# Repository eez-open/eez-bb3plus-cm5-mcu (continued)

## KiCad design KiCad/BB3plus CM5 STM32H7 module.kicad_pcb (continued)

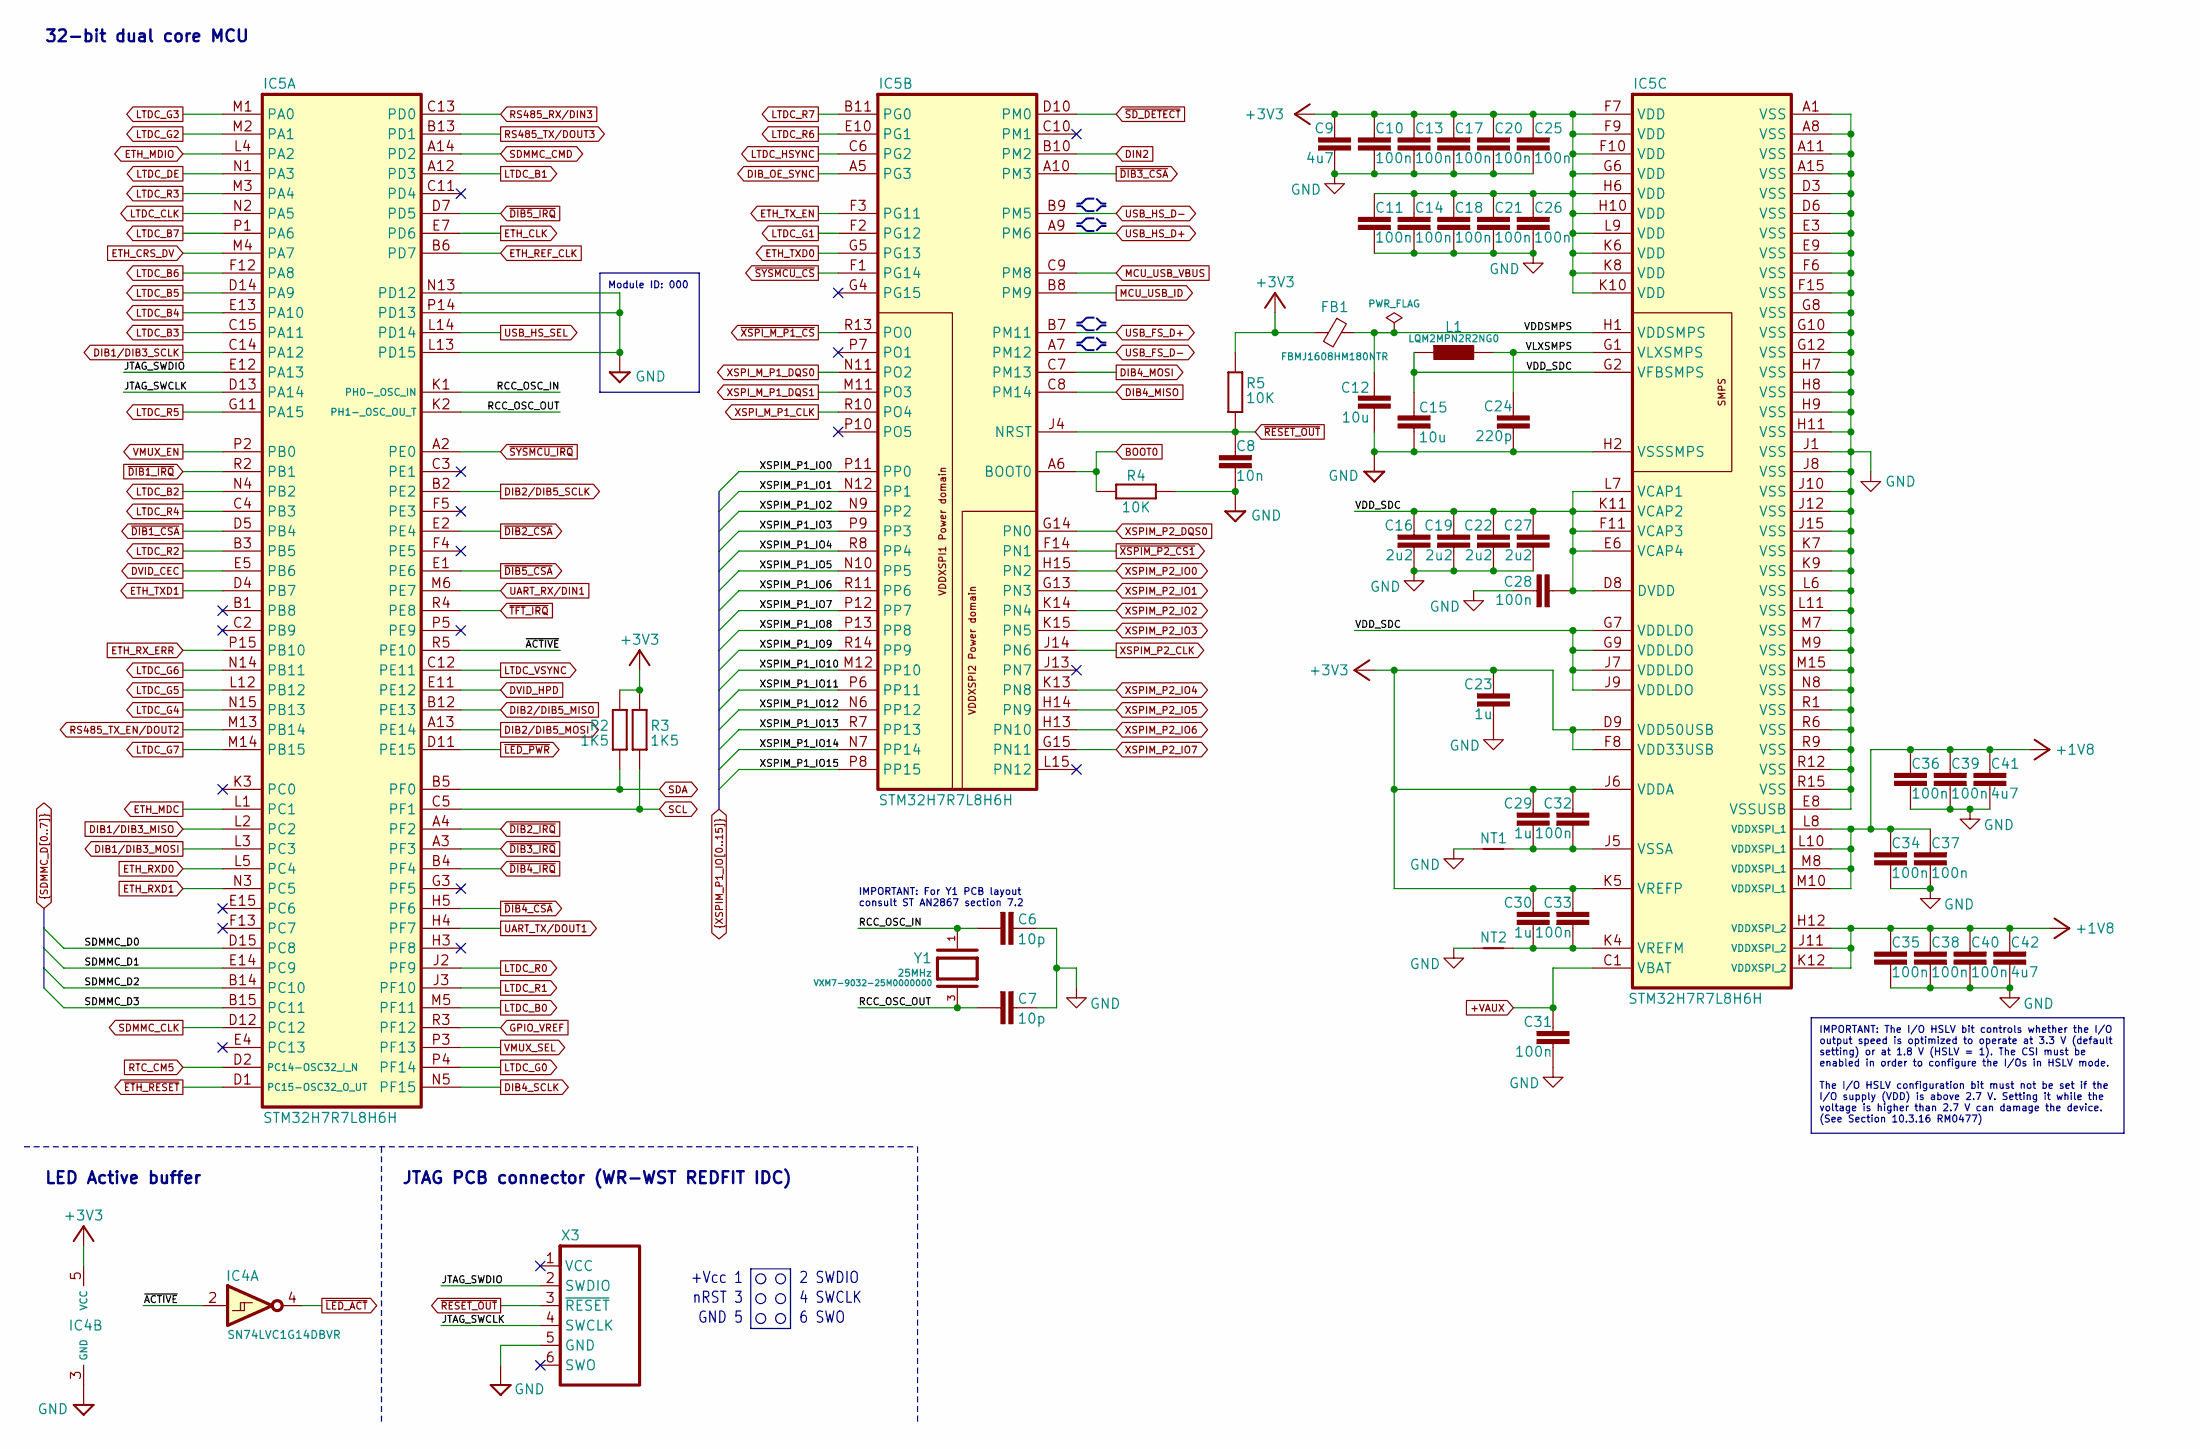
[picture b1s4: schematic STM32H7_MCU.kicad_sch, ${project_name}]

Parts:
C6, C7: 10p; C_0402_1005Metric; DigiKey 490-7299-1-ND
C8: 10n; C_0402_1005Metric; DigiKey 490-6309-1-ND
C9, C41, C42: 4u7; C_0603_1608Metric; DigiKey 1276-1044-1-ND
C10, C11, C13, C14, C17, C18, C20, C21, C25, C26, C28, C31, C32, C33, C34, C35, C36, C37, C38, C39, C40: 100n; C_0402_1005Metric; DigiKey 490-6287-1-ND
C12, C15: 10u; C_0603_1608Metric; DigiKey 1276-1052-6-ND
C16, C19, C22, C27: 2u2; C_0402_1005Metric; DigiKey 490-GRM155C71A225KE11JCT-ND
C23, C29, C30: 1u; C_0402_1005Metric; DigiKey 490-GRM155C81A105MA12DCT-ND
C24: 220p; C_0402_1005Metric; DigiKey 1276-6762-1-ND
FB1: FBMJ1608HM180NTR; BEAD0603; DigiKey 587-3251-2-ND
IC4: SN74LVC1G14DBVR; DBV5; DigiKey 296-11607-1-ND
IC5: STM32H7R7L8H6H; TFBGA225_13X13_STM; DigiKey 497-STM32H7R7L8H6H-ND
L1: LQM2MPN2R2NG0; 0806; DigiKey 490-7786-2-ND
NT1, NT2: NetTie_2; NetTie-2_SMD_Pad0.2mm
R2, R3: 1K5; R_0402_1005Metric; DigiKey 311-1.50KLRCT-ND
R4, R5: 10K; R_0402_1005Metric; DigiKey 311-10.0KLRCT-ND
X3: WR-WST_490107670612_DEBUG_no frame
Y1: VXM7-9032-25M0000000; XTAL_403C11A24M00000; DigiKey 150-VXM7-9032-25M0000000CT-ND

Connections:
+1V8: C34.1, C35.1, C36.1, C37.1, C38.1, C39.1, C40.1, C41.1, C42.1, IC5.H12 (VDDXSPI_2), IC5.J11 (VDDXSPI_2), IC5.K12 (VDDXSPI_2), IC5.L8 (VDDXSPI_1), IC5.L10 (VDDXSPI_1), IC5.M8 (VDDXSPI_1), IC5.M10 (VDDXSPI_1); also elsewhere on the board
+3V3: C9.1, C10.1, C11.1, C13.1, C14.1, C17.1, C18.1, C20.1, C21.1, C23.1, C25.1, C26.1, C29.1, C30.1, C32.1, C33.1, FB1.2, IC4.5 (VCC), IC5.D9 (VDD50USB), IC5.F7 (VDD), IC5.F8 (VDD33USB), IC5.F9 (VDD), IC5.F10 (VDD), IC5.G6 (VDD), IC5.H6 (VDD), IC5.H10 (VDD), IC5.J6 (VDDA), IC5.K5 (VREFP), IC5.K6 (VDD), IC5.K8 (VDD), IC5.K10 (VDD), IC5.L9 (VDD), R2.2, R3.2, R5.2; also elsewhere on the board
+VAUX: C31.1, IC5.C1 (VBAT); also elsewhere on the board
/STM32H7 MCU/JTAG_SWCLK: IC5.D13 (PA14), X3.4 (SWCLK)
/STM32H7 MCU/JTAG_SWDIO: IC5.E12 (PA13), X3.2 (SWDIO)
/STM32H7 MCU/RCC_OSC_IN: C6.2, IC5.K1 (PH0-_OSC_IN), Y1.1
/STM32H7 MCU/RCC_OSC_OUT: C7.2, IC5.K2 (PH1-_OSC_OU_T), Y1.3
/STM32H7 MCU/VDDSMPS: C12.2, FB1.1, IC5.H1 (VDDSMPS)
/STM32H7 MCU/VDD_SDC: C15.2, C16.1, C19.1, C22.1, C27.1, C28.2, IC5.D8 (DVDD), IC5.E6 (VCAP4), IC5.F11 (VCAP3), IC5.G2 (VFBSMPS), IC5.G7 (VDDLDO), IC5.G9 (VDDLDO), IC5.J7 (VDDLDO), IC5.J9 (VDDLDO), IC5.K11 (VCAP2), IC5.L7 (VCAP1), L1.1
/STM32H7 MCU/VLXSMPS: C24.1, IC5.G1 (VLXSMPS), L1.2
/STM32H7 MCU/~ACTIVE: IC4.2 (A), IC5.R5 (PE10)
BOOT0: IC5.A6 (BOOT0), R4.1; also elsewhere on the board
DIB1/DIB3_MISO: IC5.L2 (PC2); also elsewhere on the board
DIB1/DIB3_MOSI: IC5.L3 (PC3); also elsewhere on the board
DIB1/DIB3_SCLK: IC5.C14 (PA12); also elsewhere on the board
DIB2/DIB5_MISO: IC5.B12 (PE13); also elsewhere on the board
DIB2/DIB5_MOSI: IC5.A13 (PE14); also elsewhere on the board
DIB2/DIB5_SCLK: IC5.B2 (PE2); also elsewhere on the board
DIB4_MISO: IC5.C8 (PM14); also elsewhere on the board
DIB4_MOSI: IC5.C7 (PM13); also elsewhere on the board
DIB4_SCLK: IC5.N5 (PF15); also elsewhere on the board
DIB_OE_SYNC: IC5.A5 (PG3); also elsewhere on the board
DIN2: IC5.B10 (PM2); also elsewhere on the board
DVID_CEC: IC5.E5 (PB6); also elsewhere on the board
DVID_HPD: IC5.E11 (PE12); also elsewhere on the board
ETH_CLK: IC5.E7 (PD6); also elsewhere on the board
ETH_CRS_DV: IC5.M4 (PA7); also elsewhere on the board
ETH_MDC: IC5.L1 (PC1); also elsewhere on the board
ETH_MDIO: IC5.L4 (PA2); also elsewhere on the board
ETH_REF_CLK: IC5.B6 (PD7); also elsewhere on the board
ETH_RXD0: IC5.L5 (PC4); also elsewhere on the board
ETH_RXD1: IC5.N3 (PC5); also elsewhere on the board
ETH_RX_ERR: IC5.P15 (PB10); also elsewhere on the board
ETH_TXD0: IC5.G5 (PG13); also elsewhere on the board
ETH_TXD1: IC5.D4 (PB7); also elsewhere on the board
ETH_TX_EN: IC5.F3 (PG11); also elsewhere on the board
GND: C6.1, C7.1, C8.2, C9.2, C10.2, C11.2, C12.1, C13.2, C14.2, C15.1, C16.2, C17.2, C18.2, C19.2, C20.2, C21.2, C22.2, C23.2, C24.2, C25.2, C26.2, C27.2, C28.1, C31.2, C34.2, C35.2, C36.2, C37.2, C38.2, C39.2, C40.2, C41.2, C42.2, IC4.3 (GND), IC5.A1 (VSS), IC5.A8 (VSS), IC5.A11 (VSS), IC5.A15 (VSS), IC5.D3 (VSS), IC5.D6 (VSS), IC5.E3 (VSS), IC5.E8 (VSSUSB), IC5.E9 (VSS), IC5.F6 (VSS), IC5.F15 (VSS), IC5.G8 (VSS), IC5.G10 (VSS), IC5.G12 (VSS), IC5.H2 (VSSSMPS), IC5.H7 (VSS), IC5.H8 (VSS), IC5.H9 (VSS), IC5.H11 (VSS), IC5.J1 (VSS), IC5.J8 (VSS), IC5.J10 (VSS), IC5.J12 (VSS), IC5.J15 (VSS), IC5.K7 (VSS), IC5.K9 (VSS), IC5.L6 (VSS), IC5.L11 (VSS), IC5.L13 (PD15), IC5.M7 (VSS), IC5.M9 (VSS), IC5.M15 (VSS), IC5.N8 (VSS), IC5.N13 (PD12), IC5.P14 (PD13), IC5.R1 (VSS), IC5.R6 (VSS), IC5.R9 (VSS), IC5.R12 (VSS), IC5.R15 (VSS), NT1.1, NT2.1, R4.2, X3.5 (GND); also elsewhere on the board
GPIO_VREF: IC5.R3 (PF12); also elsewhere on the board
LTDC_B0: IC5.M5 (PF11); also elsewhere on the board
LTDC_B1: IC5.A12 (PD3); also elsewhere on the board
LTDC_B2: IC5.N4 (PB2); also elsewhere on the board
LTDC_B3: IC5.C15 (PA11); also elsewhere on the board
LTDC_B4: IC5.E13 (PA10); also elsewhere on the board
LTDC_B5: IC5.D14 (PA9); also elsewhere on the board
LTDC_B6: IC5.F12 (PA8); also elsewhere on the board
LTDC_B7: IC5.P1 (PA6); also elsewhere on the board
LTDC_CLK: IC5.N2 (PA5); also elsewhere on the board
LTDC_DE: IC5.N1 (PA3); also elsewhere on the board
LTDC_G0: IC5.P4 (PF14); also elsewhere on the board
LTDC_G1: IC5.F2 (PG12); also elsewhere on the board
LTDC_G2: IC5.M2 (PA1); also elsewhere on the board
LTDC_G3: IC5.M1 (PA0); also elsewhere on the board
LTDC_G4: IC5.N15 (PB13); also elsewhere on the board
LTDC_G5: IC5.L12 (PB12); also elsewhere on the board
LTDC_G6: IC5.N14 (PB11); also elsewhere on the board
LTDC_G7: IC5.M14 (PB15); also elsewhere on the board
LTDC_HSYNC: IC5.C6 (PG2); also elsewhere on the board
LTDC_R0: IC5.J2 (PF9); also elsewhere on the board
LTDC_R1: IC5.J3 (PF10); also elsewhere on the board
LTDC_R2: IC5.B3 (PB5); also elsewhere on the board
LTDC_R3: IC5.M3 (PA4); also elsewhere on the board
LTDC_R4: IC5.C4 (PB3); also elsewhere on the board
LTDC_R5: IC5.G11 (PA15); also elsewhere on the board
LTDC_R6: IC5.E10 (PG1); also elsewhere on the board
LTDC_R7: IC5.B11 (PG0); also elsewhere on the board
LTDC_VSYNC: IC5.C12 (PE11); also elsewhere on the board
MCU_USB_ID: IC5.B8 (PM9); also elsewhere on the board
MCU_USB_VBUS: IC5.C9 (PM8); also elsewhere on the board
unnamed: C30.2, C33.2, IC5.K4 (VREFM), NT2.2
unnamed: C29.2, C32.2, IC5.J5 (VSSA), NT1.2
RS485_RX/DIN3: IC5.C13 (PD0); also elsewhere on the board
RS485_TX_EN/DOUT2: IC5.M13 (PB14); also elsewhere on the board
RS485_TX/DOUT3: IC5.B13 (PD1); also elsewhere on the board
RTC_CM5: IC5.D2 (PC14-OSC32_I_N); also elsewhere on the board
SCL: IC5.C5 (PF1), R3.1; also elsewhere on the board
SDA: IC5.B5 (PF0), R2.1; also elsewhere on the board
SDMMC_CLK: IC5.D12 (PC12); also elsewhere on the board
SDMMC_CMD: IC5.A14 (PD2); also elsewhere on the board
SDMMC_D0: IC5.D15 (PC8); also elsewhere on the board
SDMMC_D1: IC5.E14 (PC9); also elsewhere on the board
SDMMC_D2: IC5.B14 (PC10); also elsewhere on the board
SDMMC_D3: IC5.B15 (PC11); also elsewhere on the board
UART_RX/DIN1: IC5.M6 (PE7); also elsewhere on the board
UART_TX/DOUT1: IC5.H4 (PF7); also elsewhere on the board
USB_FS_D+: IC5.B7 (PM11); also elsewhere on the board
USB_FS_D-: IC5.A7 (PM12); also elsewhere on the board
USB_HS_D+: IC5.A9 (PM6); also elsewhere on the board
USB_HS_D-: IC5.B9 (PM5); also elsewhere on the board
USB_HS_SEL: IC5.L14 (PD14); also elsewhere on the board
VMUX_EN: IC5.P2 (PB0); also elsewhere on the board
VMUX_SEL: IC5.P3 (PF13); also elsewhere on the board
XSPIM_P1_IO0: IC5.P11 (PP0); also elsewhere on the board
XSPIM_P1_IO1: IC5.N12 (PP1); also elsewhere on the board
XSPIM_P1_IO2: IC5.N9 (PP2); also elsewhere on the board
XSPIM_P1_IO3: IC5.P9 (PP3); also elsewhere on the board
XSPIM_P1_IO4: IC5.R8 (PP4); also elsewhere on the board
XSPIM_P1_IO5: IC5.N10 (PP5); also elsewhere on the board
XSPIM_P1_IO6: IC5.R11 (PP6); also elsewhere on the board
XSPIM_P1_IO7: IC5.P12 (PP7); also elsewhere on the board
XSPIM_P1_IO8: IC5.P13 (PP8); also elsewhere on the board
XSPIM_P1_IO9: IC5.R14 (PP9); also elsewhere on the board
XSPIM_P1_IO10: IC5.M12 (PP10); also elsewhere on the board
XSPIM_P1_IO11: IC5.P6 (PP11); also elsewhere on the board
XSPIM_P1_IO12: IC5.N6 (PP12); also elsewhere on the board
XSPIM_P1_IO13: IC5.R7 (PP13); also elsewhere on the board
XSPIM_P1_IO14: IC5.N7 (PP14); also elsewhere on the board
XSPIM_P1_IO15: IC5.P8 (PP15); also elsewhere on the board
XSPIM_P2_CLK: IC5.J14 (PN6); also elsewhere on the board
XSPIM_P2_DQS0: IC5.G14 (PN0); also elsewhere on the board
XSPIM_P2_IO0: IC5.H15 (PN2); also elsewhere on the board
XSPIM_P2_IO1: IC5.G13 (PN3); also elsewhere on the board
XSPIM_P2_IO2: IC5.K14 (PN4); also elsewhere on the board
XSPIM_P2_IO3: IC5.K15 (PN5); also elsewhere on the board
XSPIM_P2_IO4: IC5.K13 (PN8); also elsewhere on the board
XSPIM_P2_IO5: IC5.H14 (PN9); also elsewhere on the board
XSPIM_P2_IO6: IC5.H13 (PN10); also elsewhere on the board
XSPIM_P2_IO7: IC5.G15 (PN11); also elsewhere on the board
XSPI_M_P1_CLK: IC5.R10 (PO4); also elsewhere on the board
XSPI_M_P1_DQS0: IC5.N11 (PO2); also elsewhere on the board
XSPI_M_P1_DQS1: IC5.M11 (PO3); also elsewhere on the board
~DIB1_CSA: IC5.D5 (PB4); also elsewhere on the board
~DIB1_IRQ: IC5.R2 (PB1); also elsewhere on the board
~DIB2_CSA: IC5.E2 (PE4); also elsewhere on the board
~DIB2_IRQ: IC5.A4 (PF2); also elsewhere on the board
~DIB3_CSA: IC5.A10 (PM3); also elsewhere on the board
~DIB3_IRQ: IC5.A3 (PF3); also elsewhere on the board
~DIB4_CSA: IC5.H5 (PF6); also elsewhere on the board
~DIB4_IRQ: IC5.B4 (PF4); also elsewhere on the board
~DIB5_CSA: IC5.E1 (PE6); also elsewhere on the board
~DIB5_IRQ: IC5.D7 (PD5); also elsewhere on the board
~ETH_RESET: IC5.D1 (PC15-OSC32_O_UT); also elsewhere on the board
~LED_ACT: IC4.4 (Y); also elsewhere on the board
~LED_PWR: IC5.D11 (PE15); also elsewhere on the board
~RESET_OUT: C8.1, IC5.J4 (NRST), R5.1, X3.3 (~RESET); also elsewhere on the board
~SD_DETECT: IC5.D10 (PM0); also elsewhere on the board
~SYSMCU_CS: IC5.F1 (PG14); also elsewhere on the board
~SYSMCU_IRQ: IC5.A2 (PE0); also elsewhere on the board
~TFT_IRQ: IC5.R4 (PE8); also elsewhere on the board
~XSPIM_P2_CS1: IC5.F14 (PN1); also elsewhere on the board
~XSPI_M_P1_CS: IC5.R13 (PO0); also elsewhere on the board

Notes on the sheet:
2 SWDIO
32-bit dual core MCU
LED Active buffer
4 SWCLK
6 SWO
JTAG PCB connector (WR-WST REDFIT IDC)
nRST 3
IMPORTANT: For Y1 PCB layout consult ST AN2867 section 7.2
+Vcc 1
GND 5
IMPORTANT: The I/O HSLV bit controls whether the I/O output speed is optimized to operate at 3.3 V (default setting) or at 1.8 V (HSLV = 1). The CSI must be enabled in order to configure the I/Os in HSLV mode. The I/O HSLV configuration bit must not be set if the I/O supply (VDD) is above 2.7 V. Se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
Module ID: 000

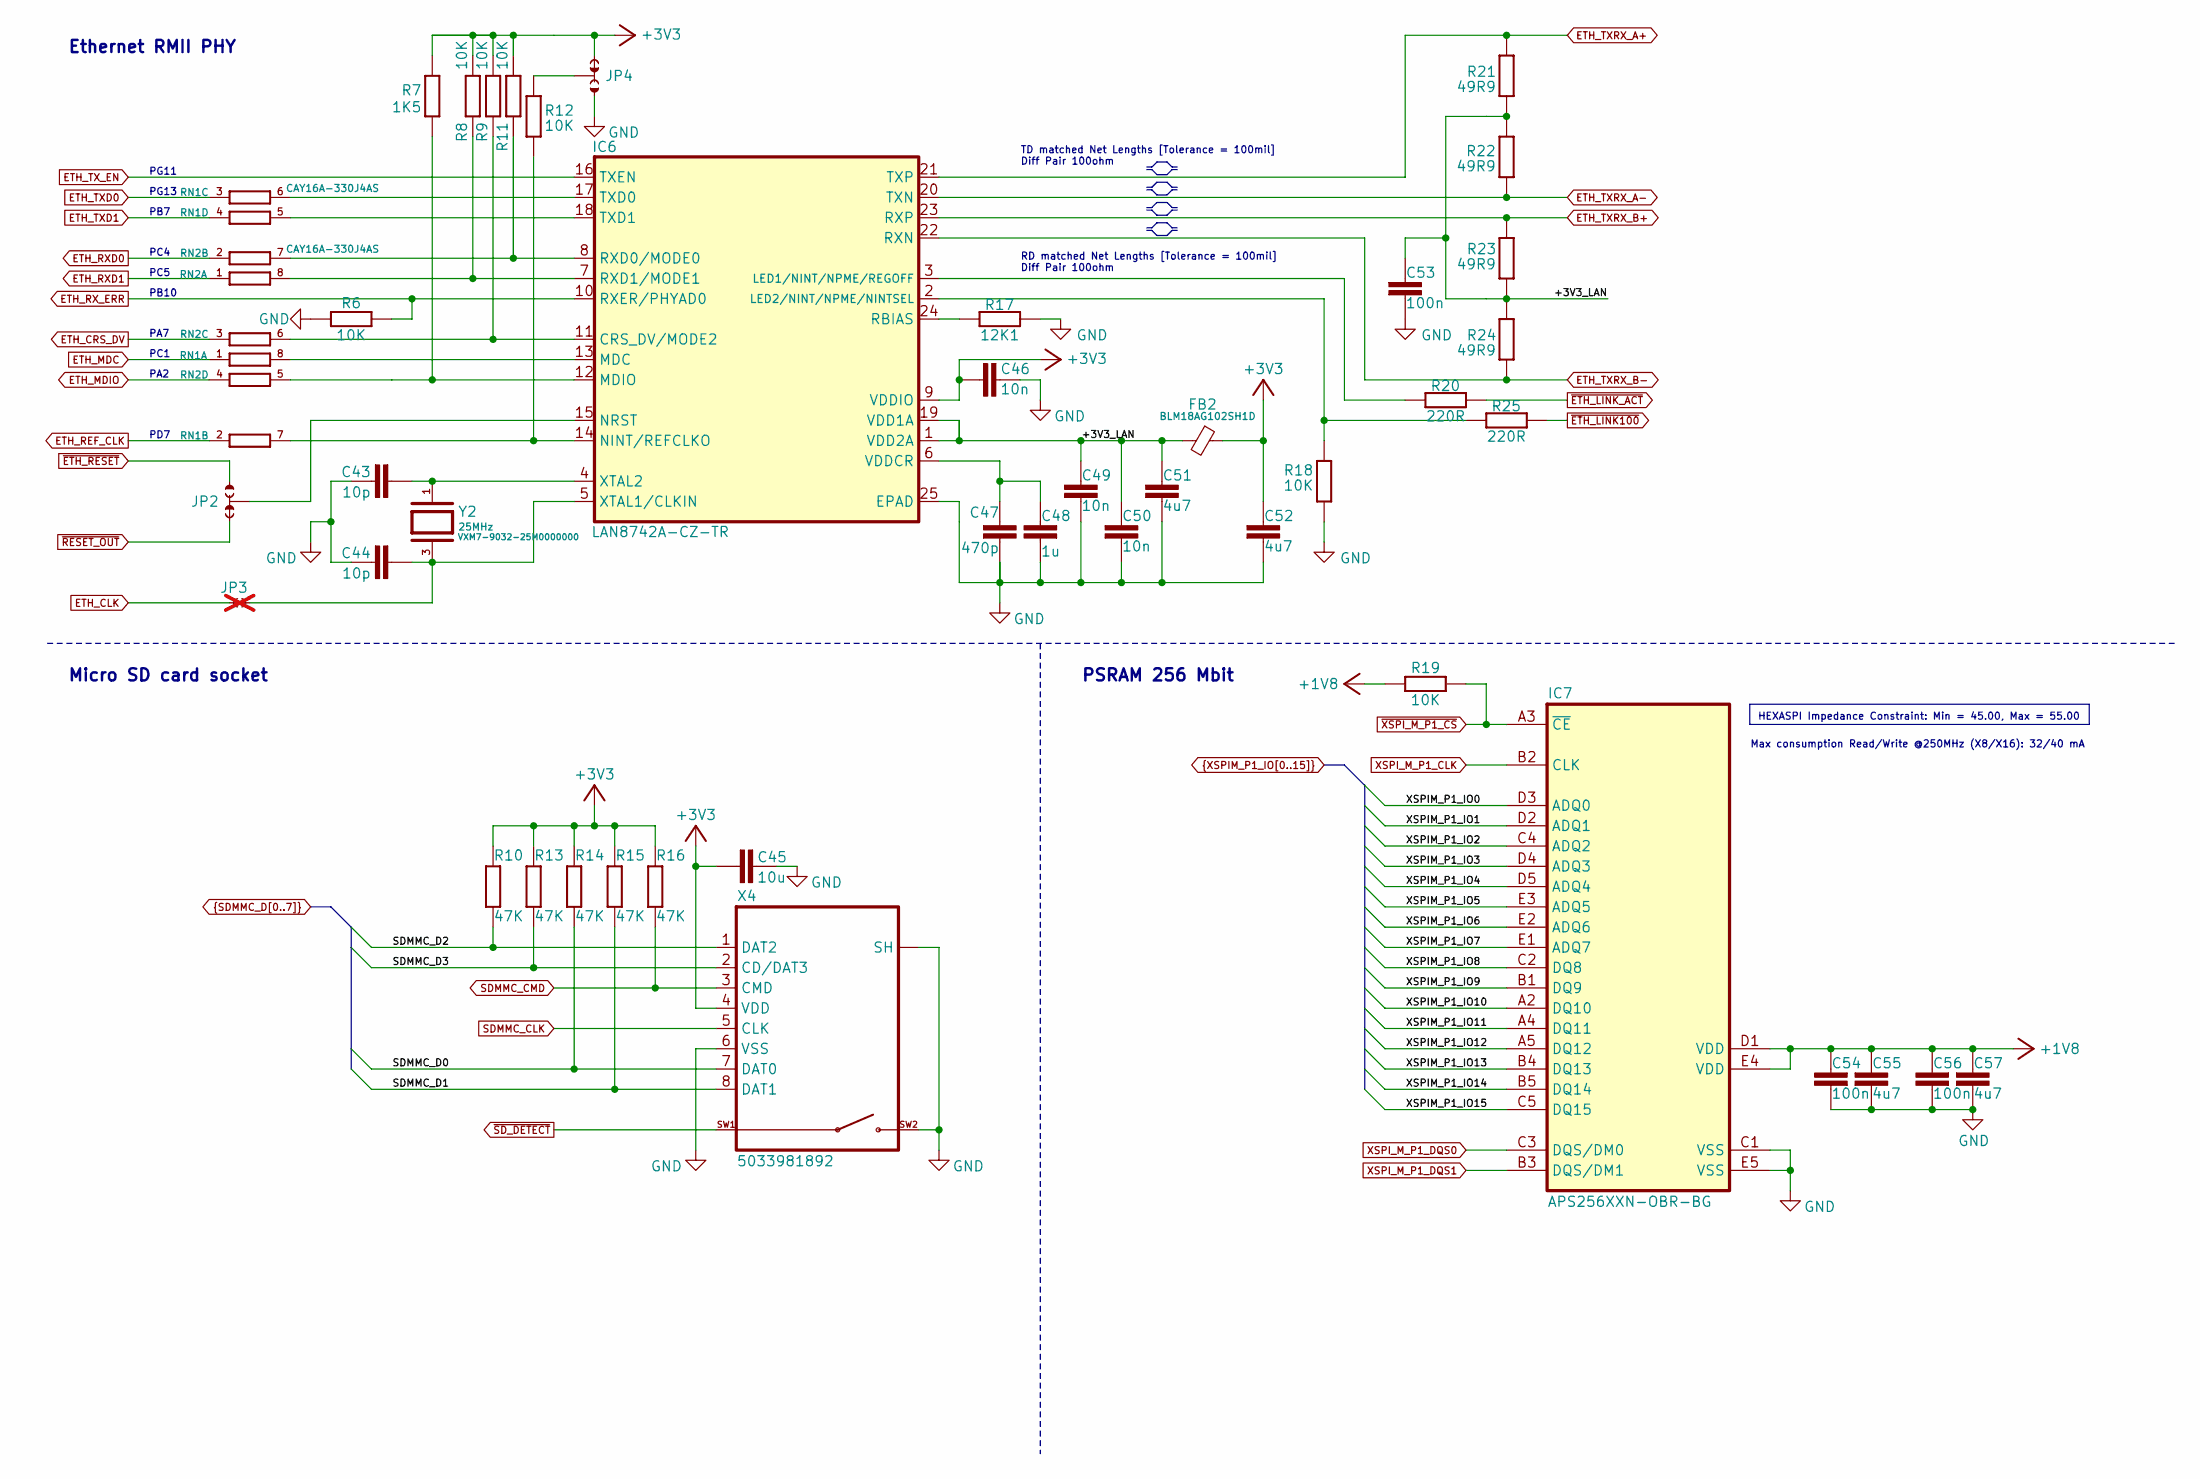
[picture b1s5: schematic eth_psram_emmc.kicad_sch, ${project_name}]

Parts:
C43, C44: 10p; C_0402_1005Metric; DigiKey 490-7299-1-ND
C45: 10u; C_0603_1608Metric; DigiKey 1276-1052-6-ND
C46, C49, C50: 10n; C_0402_1005Metric; DigiKey 490-6309-1-ND
C47: 470p; C_0402_1005Metric; DigiKey 1276-1117-1-ND
C48: 1u; C_0402_1005Metric; DigiKey 490-GRM155C81A105MA12DCT-ND
C51, C52, C55, C57: 4u7; C_0603_1608Metric; DigiKey 1276-1044-1-ND
C53, C54, C56: 100n; C_0402_1005Metric; DigiKey 490-6287-1-ND
FB2: BLM18AG102SH1D; BEAD0603; DigiKey 490-7809-1-ND
IC6: LAN8742A-CZ-TR; SQFN24_4X4MC_MCH-M; DigiKey LAN8742A-CZ-CT-ND
IC7: APS256XXN-OBR-BG; APS256XXN-OBR-BG_APY-L; Mouser 878-APS256XXN-OB9-BG
JP2, JP4: JP3 shorted (0603)
JP3: JP2 open (0402); not fitted
R6, R8, R9, R11, R12, R18, R19: 10K; R_0402_1005Metric; DigiKey 311-10.0KLRCT-ND
R7: 1K5; R_0402_1005Metric; DigiKey 311-1.50KLRCT-ND
R10, R13, R14, R15, R16: 47K; R_0402_1005Metric; DigiKey 311-47.0KLRCT-ND
R17: 12K1; R_0402_1005Metric; DigiKey 13-RC0402FR-1012K1LCT-ND
R20, R25: 220R; R_0402_1005Metric; DigiKey 311-220LRCT-ND
R21, R22, R23, R24: 49R9; R_0402_1005Metric; DigiKey 13-RC0402FR-1349R9LCT-ND
RN1, RN2: CAY16A-330J4AS; CAY16; DigiKey CAY16-330J4LFCT-ND
X4: 5033981892; DigiKey WM11190CT-ND
Y2: VXM7-9032-25M0000000; XTAL_403C11A24M00000; DigiKey 150-VXM7-9032-25M0000000CT-ND

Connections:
+1V8: C54.1, C55.1, C56.1, C57.1, IC7.D1 (VDD), IC7.E4 (VDD), R19.2; also elsewhere on the board
+3V3: C45.2, C46.1, C52.1, FB2.1, IC6.9 (VDDIO), JP4.NC, R7.2, R8.1, R9.2, R10.1, R11.2, R13.1, R14.1, R15.1, R16.1, X4.4 (VDD); also elsewhere on the board
/Ethernet PHY, PSRAM, SDcard/+3V3_LAN: C49.1, C50.1, C51.1, C53.2, FB2.2, IC6.1 (VDD2A), IC6.19 (VDD1A), R21.1, R22.1, R23.1, R24.2
ETH_CLK: JP3.1; also elsewhere on the board
ETH_CRS_DV: RN2.3 (1); also elsewhere on the board
ETH_MDC: RN1.1; also elsewhere on the board
ETH_MDIO: RN2.4 (1); also elsewhere on the board
ETH_REF_CLK: RN1.2 (1); also elsewhere on the board
ETH_RXD0: RN2.2 (1); also elsewhere on the board
ETH_RXD1: RN2.1; also elsewhere on the board
ETH_RX_ERR: IC6.10 (RXER/PHYAD0), R6.1; also elsewhere on the board
ETH_TXD0: RN1.3 (1); also elsewhere on the board
ETH_TXD1: RN1.4 (1); also elsewhere on the board
ETH_TXRX_A+: IC6.21 (TXP), R21.2; also elsewhere on the board
ETH_TXRX_A-: IC6.20 (TXN), R22.2; also elsewhere on the board
ETH_TXRX_B+: IC6.23 (RXP), R23.2; also elsewhere on the board
ETH_TXRX_B-: IC6.22 (RXN), R24.1; also elsewhere on the board
ETH_TX_EN: IC6.16 (TXEN); also elsewhere on the board
GND: C43.1, C44.1, C45.1, C46.2, C47.2, C48.1, C49.2, C50.2, C51.2, C52.2, C53.1, C54.2, C55.2, C56.2, C57.2, IC6.25 (EPAD), IC7.C1 (VSS), IC7.E5 (VSS), JP4.NO, R6.2, R17.2, R18.2, X4.6 (VSS), X4.SH, X4.SW2; also elsewhere on the board
unnamed: IC6.11 (CRS_DV/MODE2), R9.1, RN2.6 (2)
unnamed: IC6.3 (LED1/NINT/NPME/REGOFF), R20.1
unnamed: IC6.2 (LED2/NINT/NPME/NINTSEL), R18.1, R25.1
unnamed: IC6.13 (MDC), RN1.8 (2)
unnamed: IC6.12 (MDIO), R7.1, RN2.5 (2)
unnamed: IC6.14 (NINT/REFCLKO), R12.1, RN1.7 (2)
unnamed: IC6.15 (NRST), JP2.COM
unnamed: IC6.24 (RBIAS), R17.1
unnamed: IC6.8 (RXD0/MODE0), R11.1, RN2.7 (2)
unnamed: IC6.7 (RXD1/MODE1), R8.2, RN2.8 (2)
unnamed: IC6.17 (TXD0), RN1.6 (2)
unnamed: IC6.18 (TXD1), RN1.5 (2)
unnamed: C47.1, C48.2, IC6.6 (VDDCR)
unnamed: C44.2, IC6.5 (XTAL1/CLKIN), JP3.2, Y2.3
unnamed: C43.2, IC6.4 (XTAL2), Y2.1
unnamed: JP4.COM, R12.2
SDMMC_CLK: X4.5 (CLK); also elsewhere on the board
SDMMC_CMD: R16.2, X4.3 (CMD); also elsewhere on the board
SDMMC_D0: R14.2, X4.7 (DAT0); also elsewhere on the board
SDMMC_D1: R15.2, X4.8 (DAT1); also elsewhere on the board
SDMMC_D2: R10.2, X4.1 (DAT2); also elsewhere on the board
SDMMC_D3: R13.2, X4.2 (CD/DAT3); also elsewhere on the board
XSPIM_P1_IO0: IC7.D3 (ADQ0); also elsewhere on the board
XSPIM_P1_IO1: IC7.D2 (ADQ1); also elsewhere on the board
XSPIM_P1_IO2: IC7.C4 (ADQ2); also elsewhere on the board
XSPIM_P1_IO3: IC7.D4 (ADQ3); also elsewhere on the board
XSPIM_P1_IO4: IC7.D5 (ADQ4); also elsewhere on the board
XSPIM_P1_IO5: IC7.E3 (ADQ5); also elsewhere on the board
XSPIM_P1_IO6: IC7.E2 (ADQ6); also elsewhere on the board
XSPIM_P1_IO7: IC7.E1 (ADQ7); also elsewhere on the board
XSPIM_P1_IO8: IC7.C2 (DQ8); also elsewhere on the board
XSPIM_P1_IO9: IC7.B1 (DQ9); also elsewhere on the board
XSPIM_P1_IO10: IC7.A2 (DQ10); also elsewhere on the board
XSPIM_P1_IO11: IC7.A4 (DQ11); also elsewhere on the board
XSPIM_P1_IO12: IC7.A5 (DQ12); also elsewhere on the board
XSPIM_P1_IO13: IC7.B4 (DQ13); also elsewhere on the board
XSPIM_P1_IO14: IC7.B5 (DQ14); also elsewhere on the board
XSPIM_P1_IO15: IC7.C5 (DQ15); also elsewhere on the board
XSPI_M_P1_CLK: IC7.B2 (CLK); also elsewhere on the board
XSPI_M_P1_DQS0: IC7.C3 (DQS/DM0); also elsewhere on the board
XSPI_M_P1_DQS1: IC7.B3 (DQS/DM1); also elsewhere on the board
~ETH_LINK100: R25.2; also elsewhere on the board
~ETH_LINK_ACT: R20.2; also elsewhere on the board
~ETH_RESET: JP2.NO; also elsewhere on the board
~RESET_OUT: JP2.NC; also elsewhere on the board
~SD_DETECT: X4.SW1; also elsewhere on the board
~XSPI_M_P1_CS: IC7.A3 (~CE), R19.1; also elsewhere on the board

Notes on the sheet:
PD7
PG11
TD matched Net Lengths [Tolerance = 100mil] Diff Pair 100ohm
Micro SD card socket
PG13
PA7
PB10
PSRAM 256 Mbit
Max consumption Read/Write @250MHz (X8/X16): 32/40 mA
PC4
PB7
PA2
Ethernet RMII PHY
RD matched Net Lengths [Tolerance = 100mil] Diff Pair 100ohm
PC5
PC1
HEXASPI Impedance Constraint: Min = 45.00, Max = 55.00

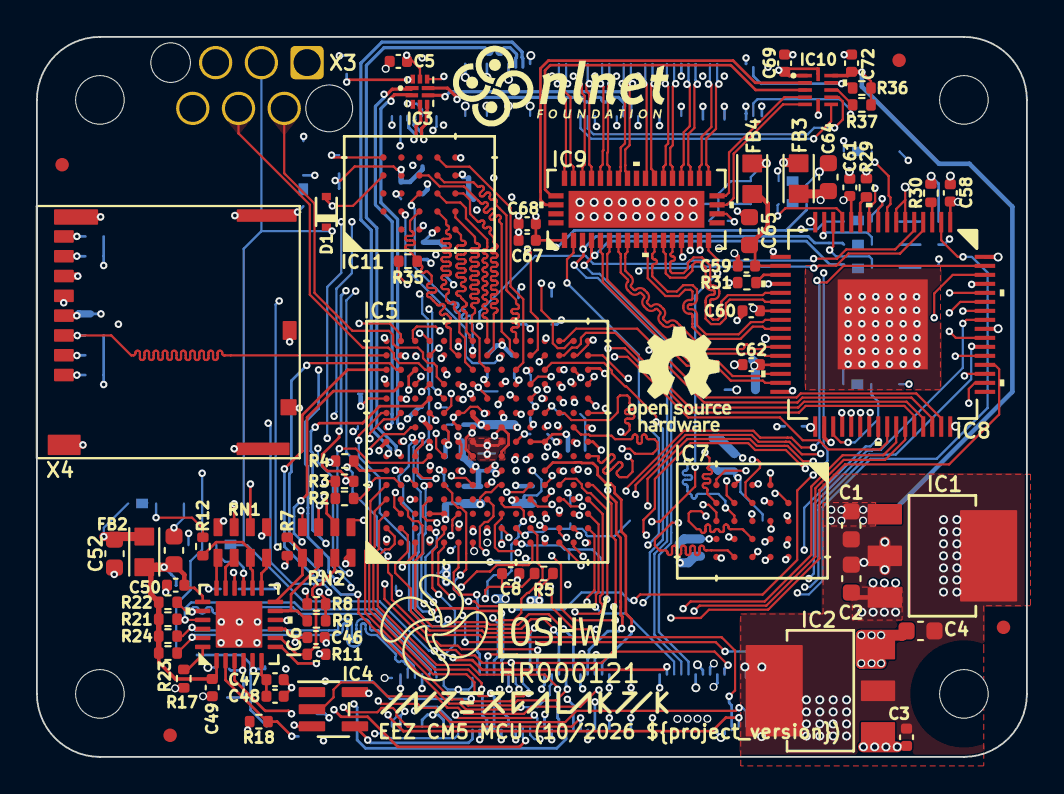
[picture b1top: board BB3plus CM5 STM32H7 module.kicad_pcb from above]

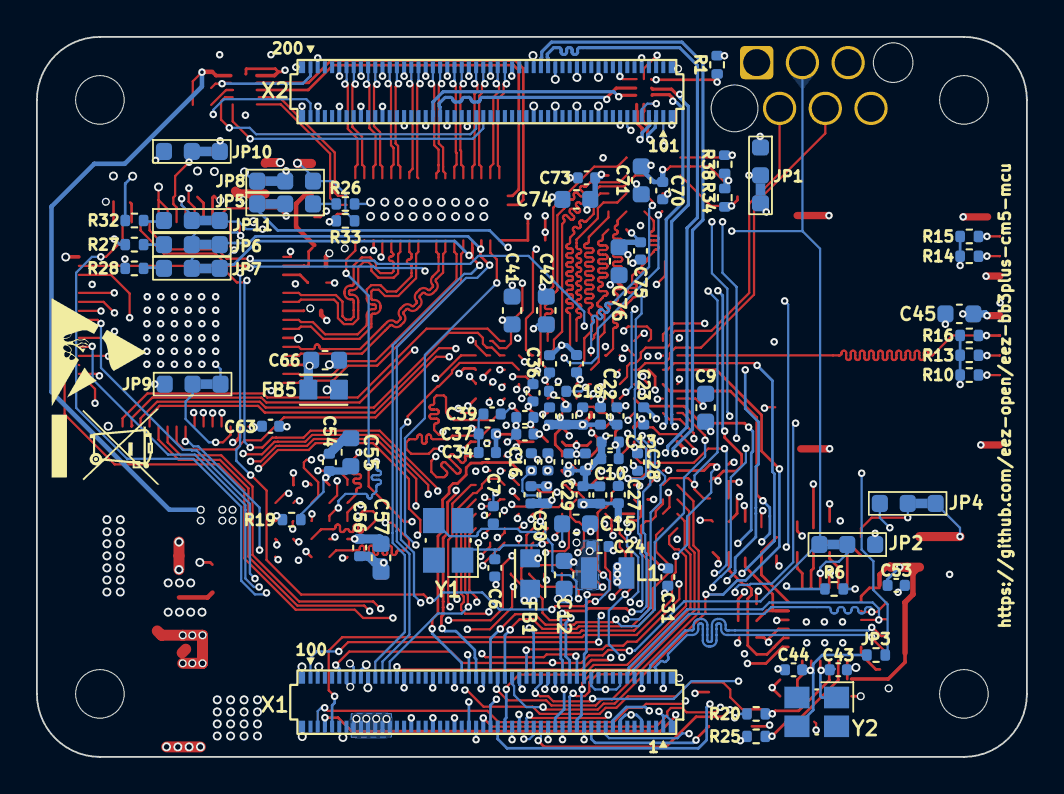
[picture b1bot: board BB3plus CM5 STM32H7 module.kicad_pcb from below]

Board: 6 copper layers, 55.0 x 40.0 mm, 164 parts (89 on the bottom side), 221 nets.

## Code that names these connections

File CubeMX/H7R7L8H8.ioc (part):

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Mcu.Name=STM32H7R7L8HxH
Mcu.Package=TFBGA225 HEXA SMPS
Mcu.UserName=STM32H7R7L8HxH
PA0.GPIOParameters=PinAttribute
PA0.Mode=RGB888
PA0.PinAttribute=Appli
PA0.Signal=LTDC_G3
PA1.GPIOParameters=PinAttribute
PA1.Mode=RGB888
PA1.PinAttribute=Appli
PA1.Signal=LTDC_G2
PA10.GPIOParameters=PinAttribute
PA10.Mode=RGB888
PA10.PinAttribute=Appli
PA10.Signal=LTDC_B4
PA11.GPIOParameters=PinAttribute
PA11.Mode=RGB888
PA11.PinAttribute=Appli
PA11.Signal=LTDC_B3
PA12.GPIOParameters=GPIO_Label,PinAttribute
PA12.GPIO_Label=DIB1/DIB3_SCK
PA12.Mode=Full_Duplex_Master
PA12.PinAttribute=Appli
PA12.Signal=SPI2_SCK
PA13(JTMS/SWDIO).GPIOParameters=GPIO_Label
PA13(JTMS/SWDIO).GPIO_Label=SWDIO
PA13(JTMS/SWDIO).Mode=Serial_Wire
PA13(JTMS/SWDIO).Signal=DEBUG_JTMS-SWDIO
PA14(JTCK/SWCLK).GPIOParameters=GPIO_Label
PA14(JTCK/SWCLK).GPIO_Label=SWCLK
PA14(JTCK/SWCLK).Mode=Serial_Wire
PA14(JTCK/SWCLK).Signal=DEBUG_JTCK-SWCLK
PA15(JTDI).GPIOParameters=PinAttribute
PA15(JTDI).Mode=RGB888
PA15(JTDI).PinAttribute=Appli
PA15(JTDI).Signal=LTDC_R5
PA2.GPIOParameters=GPIO_Speed,PinAttribute
PA2.GPIO_Speed=GPIO_SPEED_FREQ_LOW
PA2.Mode=RMII
PA2.PinAttribute=Appli
PA2.Signal=ETH_MDIO
PA3.GPIOParameters=PinAttribute
PA3.Mode=RGB888
PA3.PinAttribute=Appli
PA3.Signal=LTDC_DE
PA4.GPIOParameters=PinAttribute
PA4.Mode=RGB888
PA4.PinAttribute=Appli
PA4.Signal=LTDC_R3
PA5.GPIOParameters=PinAttribute
PA5.Mode=RGB888
PA5.PinAttribute=Appli
PA5.Signal=LTDC_CLK
PA6.GPIOParameters=PinAttribute
PA6.Mode=RGB888
PA6.PinAttribute=Appli
PA6.Signal=LTDC_B7
PA7.GPIOParameters=GPIO_Speed,PinAttribute
PA7.GPIO_Speed=GPIO_SPEED_FREQ_LOW
PA7.Mode=RMII
PA7.PinAttribute=Appli
PA7.Signal=ETH_RMII_CRS_DV
PA8.GPIOParameters=PinAttribute
PA8.Mode=RGB888
PA8.PinAttribute=Appli
PA8.Signal=LTDC_B6
PA9.GPIOParameters=PinAttribute
PA9.Mode=RGB888
PA9.PinAttribute=Appli
PA9.Signal=LTDC_B5
PB0.ContextOwner=Appli
PB0.GPIOParameters=GPIO_Label,PinAttribute
PB0.GPIO_Label=VMUX_EN
PB0.PinAttribute=Appli
PB0.Signal=GPIO_Output
PB1.ContextOwner=Appli
PB1.GPIOParameters=GPIO_Label,PinAttribute
PB1.GPIO_Label=DIB1_IRQ
PB1.PinAttribute=Appli
PB1.Signal=GPXTI1
PB10.GPIOParameters=PinAttribute
PB10.PinAttribute=Appli
PB10.Signal=ETH_MII_RX_ER
PB11.GPIOParameters=PinAttribute
PB11.Mode=RGB888
PB11.PinAttribute=Appli
PB11.Signal=LTDC_G6
PB12.GPIOParameters=PinAttribute
PB12.Mode=RGB888
PB12.PinAttribute=Appli
PB12.Signal=LTDC_G5
PB13.GPIOParameters=PinAttribute
PB13.Mode=RGB888
PB13.PinAttribute=Appli
PB13.Signal=LTDC_G4
PB14.GPIOParameters=GPIO_Label,PinAttribute
PB14.GPIO_Label=RS485_TX_EN/DOUT2
PB14.Mode=Hardware Flow Control (RS485)
PB14.PinAttribute=Appli
PB14.Signal=UART4_DE
PB15.GPIOParameters=PinAttribute
PB15.Mode=RGB888
PB15.PinAttribute=Appli
PB15.Signal=LTDC_G7
PB2.GPIOParameters=PinAttribute
PB2.Mode=RGB888
PB2.PinAttribute=Appli
PB2.Signal=LTDC_B2
PB3(JTDO/TRACESWO).GPIOParameters=PinAttribute
PB3(JTDO/TRACESWO).Mode=RGB888
PB3(JTDO/TRACESWO).PinAttribute=Appli
PB3(JTDO/TRACESWO).Signal=LTDC_R4
PB4(NJTRST).GPIOParameters=GPIO_Label,PinAttribute
PB4(NJTRST).GPIO_Label=DIB1_CSA
PB4(NJTRST).Mode=NSS_Signal_Hard_Output
PB4(NJTRST).PinAttribute=Appli
PB4(NJTRST).Signal=SPI2_NSS
PB5.GPIOParameters=PinAttribute
PB5.Mode=RGB888
PB5.PinAttribute=Appli
PB5.Signal=LTDC_R2
PB6.GPIOParameters=GPIO_Label,PinAttribute
PB6.GPIO_Label=DVID_CEC
PB6.Mode=CEC_Activate
PB6.PinAttribute=Appli
PB6.Signal=CEC
PB7.GPIOParameters=GPIO_Speed,PinAttribute
PB7.GPIO_Speed=GPIO_SPEED_FREQ_LOW
PB7.Mode=RMII
PB7.PinAttribute=Appli
PB7.Signal=ETH_RMII_TXD1
PB8.GPIOParameters=PinAttribute
PB8.PinAttribute=Appli
PB8.Signal=SDMMC1_D4
PB9.GPIOParameters=PinAttribute
PB9.PinAttribute=Appli
PB9.Signal=SDMMC1_D5
PC1.GPIOParameters=GPIO_Speed,PinAttribute
PC1.GPIO_Speed=GPIO_SPEED_FREQ_LOW
PC1.Mode=RMII
PC1.PinAttribute=Appli
PC1.Signal=ETH_MDC
PC10.GPIOParameters=PinAttribute
PC10.Mode=SD_4_bits_Wide_bus
PC10.PinAttribute=Appli
PC10.Signal=SDMMC1_D2
PC11.GPIOParameters=PinAttribute
PC11.Mode=SD_4_bits_Wide_bus
PC11.PinAttribute=Appli
PC11.Signal=SDMMC1_D3
PC12.GPIOParameters=PinAttribute
PC12.Mode=SD_4_bits_Wide_bus
PC12.PinAttribute=Appli
PC12.Signal=SDMMC1_CK
PC14-OSC32_IN(OSC32_IN).Mode=LSE-External-Clock-Source
PC14-OSC32_IN(OSC32_IN).Signal=RCC_OSC32_IN
PC15-OSC32_OUT(OSC32_OUT).GPIOParameters=GPIO_Label
PC15-OSC32_OUT(OSC32_OUT).GPIO_Label=ETH_RESET
PC15-OSC32_OUT(OSC32_OUT).Signal=GPIO_Output
PC2.GPIOParameters=GPIO_Label,PinAttribute
PC2.GPIO_Label=DIB1/DIB3_MISO
PC2.Mode=Full_Duplex_Master
PC2.PinAttribute=Appli
PC2.Signal=SPI2_MISO
PC3.GPIOParameters=GPIO_Label,PinAttribute
PC3.GPIO_Label=DIB1/DIB3_MOSI
PC3.Mode=Full_Duplex_Master
PC3.PinAttribute=Appli
PC3.Signal=SPI2_MOSI
PC4.GPIOParameters=GPIO_Speed,PinAttribute
PC4.GPIO_Speed=GPIO_SPEED_FREQ_LOW
PC4.Mode=RMII
PC4.PinAttribute=Appli
PC4.Signal=ETH_RMII_RXD0
PC5.GPIOParameters=GPIO_Speed,PinAttribute
PC5.GPIO_Speed=GPIO_SPEED_FREQ_LOW
PC5.Mode=RMII
PC5.PinAttribute=Appli
PC5.Signal=ETH_RMII_RXD1
PC6.GPIOParameters=PinAttribute
PC6.PinAttribute=Appli
PC6.Signal=SDMMC1_D6
PC7.GPIOParameters=PinAttribute
PC7.PinAttribute=Appli
PC7.Signal=SDMMC1_D7
PC8.GPIOParameters=PinAttribute
PC8.Mode=SD_4_bits_Wide_bus
PC8.PinAttribute=Appli
PC8.Signal=SDMMC1_D0
PC9.GPIOParameters=PinAttribute
PC9.Mode=SD_4_bits_Wide_bus
PC9.PinAttribute=Appli
PC9.Signal=SDMMC1_D1
PD0.GPIOParameters=GPIO_Label,PinAttribute
PD0.GPIO_Label=RS485_RX/DIN3
PD0.Mode=Asynchronous
PD0.PinAttribute=Appli
PD0.Signal=UART4_RX
PD1.GPIOParameters=GPIO_Label,PinAttribute
PD1.GPIO_Label=RS485_TX/DOUT3
PD1.Mode=Asynchronous
PD1.PinAttribute=Appli
PD1.Signal=UART4_TX
PD14.ContextOwner=Appli
PD14.GPIOParameters=GPIO_Label,PinAttribute
PD14.GPIO_Label=USB_FS_SEL
PD14.PinAttribute=Appli
PD14.Signal=GPIO_Output
PD2.GPIOParameters=PinAttribute
PD2.Mode=SD_4_bits_Wide_bus
PD2.PinAttribute=Appli
PD2.Signal=SDMMC1_CMD
PD3.GPIOParameters=PinAttribute
PD3.Mode=RGB888
PD3.PinAttribute=Appli
PD3.Signal=LTDC_B1
PD5.ContextOwner=Appli
PD5.GPIOParameters=GPIO_Label,PinAttribute
PD5.GPIO_Label=DIB5_IRQ
PD5.PinAttribute=Appli
PD5.Signal=GPXTI5
PD6.GPIOParameters=PinAttribute
PD6.Mode=Digital_ClockEthClk
PD6.PinAttribute=Free
PD6.Signal=ETH_CLK
PD7.GPIOParameters=GPIO_Speed,PinAttribute
PD7.GPIO_Speed=GPIO_SPEED_FREQ_LOW
PD7.Mode=RMII
PD7.PinAttribute=Appli
PD7.Signal=ETH_RMII_REF_CLK
PE0.ContextOwner=Appli
PE0.GPIOParameters=GPIO_Label,PinAttribute
PE0.GPIO_Label=SYSMCU_IRQ
PE0.PinAttribute=Appli
PE0.Signal=GPXTI0
PE10.ContextOwner=Appli
PE10.GPIOParameters=GPIO_Label,PinAttribute
PE10.GPIO_Label=LED_nACT
PE10.PinAttribute=Appli
PE10.Signal=GPIO_Output
PE11.GPIOParameters=PinAttribute
PE11.Mode=RGB888
PE11.PinAttribute=Appli
PE11.Signal=LTDC_VSYNC
PE12.ContextOwner=Appli
PE12.GPIOParameters=GPIO_Label,GPIO_ModeDefaultEXTI,PinAttribute
PE12.GPIO_Label=DVID_HPD
PE12.GPIO_ModeDefaultEXTI=GPIO_MODE_IT_RISING_FALLING
PE12.PinAttribute=Appli
PE12.Signal=GPXTI12
PE13.GPIOParameters=GPIO_Label,PinAttribute
PE13.GPIO_Label=DIB2/DIB5_MISO
PE13.Mode=Full_Duplex_Master
PE13.PinAttribute=Appli
PE13.Signal=SPI4_MISO
PE14.GPIOParameters=GPIO_Label,PinAttribute
PE14.GPIO_Label=DIB2/DIB5_MOSI
PE14.Mode=Full_Duplex_Master
PE14.PinAttribute=Appli
PE14.Signal=SPI4_MOSI
PE15.ContextOwner=Appli
PE15.GPIOParameters=GPIO_Label,PinAttribute
PE15.GPIO_Label=LED_PWR
PE15.PinAttribute=Appli
PE15.Signal=GPIO_Output
PE2.GPIOParameters=GPIO_Label,PinAttribute
PE2.GPIO_Label=DIB2/DIB5_SCK
PE2.Mode=Full_Duplex_Master
PE2.PinAttribute=Appli
PE2.Signal=SPI4_SCK
PE4.GPIOParameters=GPIO_Label,PinAttribute
PE4.GPIO_Label=DIB2_CSA
PE4.Mode=NSS_Signal_Hard_Output
PE4.PinAttribute=Appli
PE4.Signal=SPI4_NSS
PE6.ContextOwner=Appli
PE6.GPIOParameters=GPIO_Label,PinAttribute
PE6.GPIO_Label=DIB5_CSA
PE6.PinAttribute=Appli
PE6.Signal=GPIO_Output
PE7.GPIOParameters=GPIO_Label,PinAttribute
PE7.GPIO_Label=UART_RX/DIN1
PE7.Mode=Asynchronous
PE7.PinAttribute=Appli
PE7.Signal=UART7_RX
PE8.ContextOwner=Appli
PE8.GPIOParameters=GPIO_Label,PinAttribute
PE8.GPIO_Label=TFT_IRQ
PE8.PinAttribute=Appli
PE8.Signal=GPXTI8
PF0.GPIOParameters=GPIO_Label,PinAttribute
PF0.GPIO_Label=SDA
PF0.Mode=I2C
PF0.PinAttribute=Appli
PF0.Signal=I2C2_SDA
PF1.GPIOParameters=GPIO_Label,PinAttribute
PF1.GPIO_Label=SCL
PF1.Mode=I2C
PF1.PinAttribute=Appli
PF1.Signal=I2C2_SCL
PF10.GPIOParameters=PinAttribute
PF10.Mode=RGB888
PF10.PinAttribute=Appli
PF10.Signal=LTDC_R1
PF11.GPIOParameters=PinAttribute
PF11.Mode=RGB888
PF11.PinAttribute=Appli
PF11.Signal=LTDC_B0
PF13.ContextOwner=Appli
PF13.GPIOParameters=GPIO_Label,PinAttribute
PF13.GPIO_Label=VMUX_SEL
PF13.PinAttribute=Appli
PF13.Signal=GPIO_Output
PF14.GPIOParameters=PinAttribute
PF14.Mode=RGB888
PF14.PinAttribute=Appli
PF14.Signal=LTDC_G0
PF15.GPIOParameters=GPIO_Label,PinAttribute
PF15.GPIO_Label=DIB4_SCK
PF15.Mode=Full_Duplex_Master
PF15.PinAttribute=Appli
PF15.Signal=SPI5_SCK
PF2.ContextOwner=Appli
PF2.GPIOParameters=GPIO_Label,PinAttribute
PF2.GPIO_Label=DIB2_IRQ
PF2.PinAttribute=Appli
PF2.Signal=GPXTI2
PF3.ContextOwner=Appli
PF3.GPIOParameters=GPIO_Label,PinAttribute

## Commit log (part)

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2025-11-02 First KiCad project commit
2025-11-03 JP1 type modifed
2025-11-03 Folders paths adjusted, Cin added to 3V3 LDO
2025-11-03 BOM update
2025-11-04 PCB layout gnd vias
2025-11-11 Small PCB layout adjustments
2025-11-17 TFT_DVID control signals on 1:2 video mux removed
2026-01-29 Gerbers update
2026-04-04 #18, OSHW ID121
2026-04-14 .step file update, migration to KiCad 10
2026-04-14 .step gfile renamed
2026-04-18 USB lanes renamed, OSHWA logo added
2026-04-18 Split SoM footprint into two separate 100-pin connectors
2026-04-18 Rename USB_FS_SEL to USB_HS_SEL
2026-04-21 Ethernet PHY no xtal variant added
